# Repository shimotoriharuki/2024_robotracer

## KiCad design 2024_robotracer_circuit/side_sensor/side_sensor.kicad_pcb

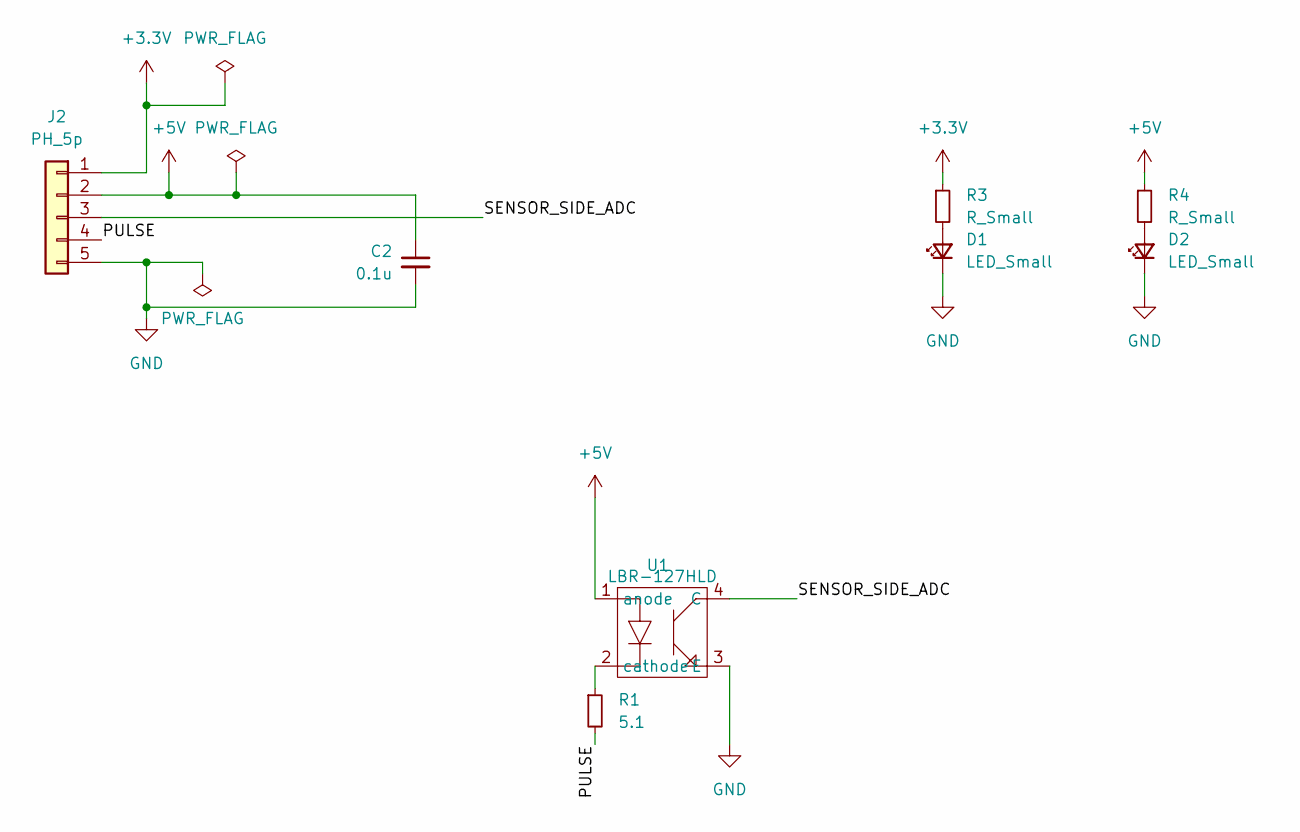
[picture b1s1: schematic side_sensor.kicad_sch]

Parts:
C2: 0.1u; C_0603_1608Metric_Pad1.08x0.95mm_HandSolder
D1, D2: LED_Small; LED_0603_1608Metric_Pad1.05x0.95mm_HandSolder
J2: PH_5p; JST_PH_B5B-PH-K_1x05_P2.00mm_Vertical
R1: 5.1; R_0603_1608Metric_Pad0.98x0.95mm_HandSolder
R3, R4: R_Small; R_0603_1608Metric_Pad0.98x0.95mm_HandSolder
U1: LBR-127HLD

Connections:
+3.3V: J2.1, R3.1
+5V: C2.1, J2.2, R4.1, U1.1 (anode)
/PULSE: J2.4, R1.2
/SENSOR_SIDE_ADC: J2.3, U1.4 (C)
GND: C2.2, D1.1 (K), D2.1 (K), J2.5, U1.3 (E)
unnamed: D1.2 (A), R3.2
unnamed: D2.2 (A), R4.2
unnamed: R1.1, U1.2 (cathode)

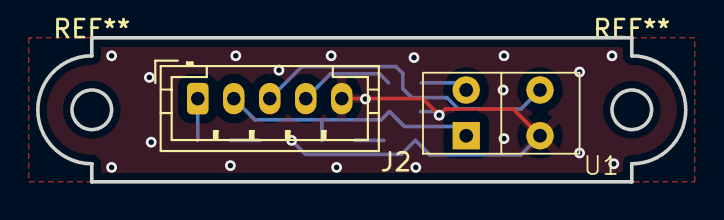
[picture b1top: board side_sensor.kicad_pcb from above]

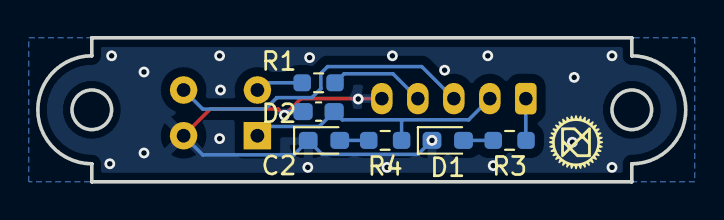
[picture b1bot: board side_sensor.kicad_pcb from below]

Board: 2 copper layers, 36.0 x 8.0 mm, 8 parts (6 on the bottom side), 8 nets.

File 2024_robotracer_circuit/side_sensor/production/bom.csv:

Designator,Footprint,Quantity,Value,LCSC Part #
C2,0603,1,0.1u,
"D1, D2",0603,2,LED_Small,
J2,JST_PH_B5B-PH-K_1x05_P2.00mm_Vertical,1,PH_5p,
R1,0603,1,4.7,
"R3, R4",0603,2,R_Small,
U1,LBR-127HLD,1,LBR-127HLD,

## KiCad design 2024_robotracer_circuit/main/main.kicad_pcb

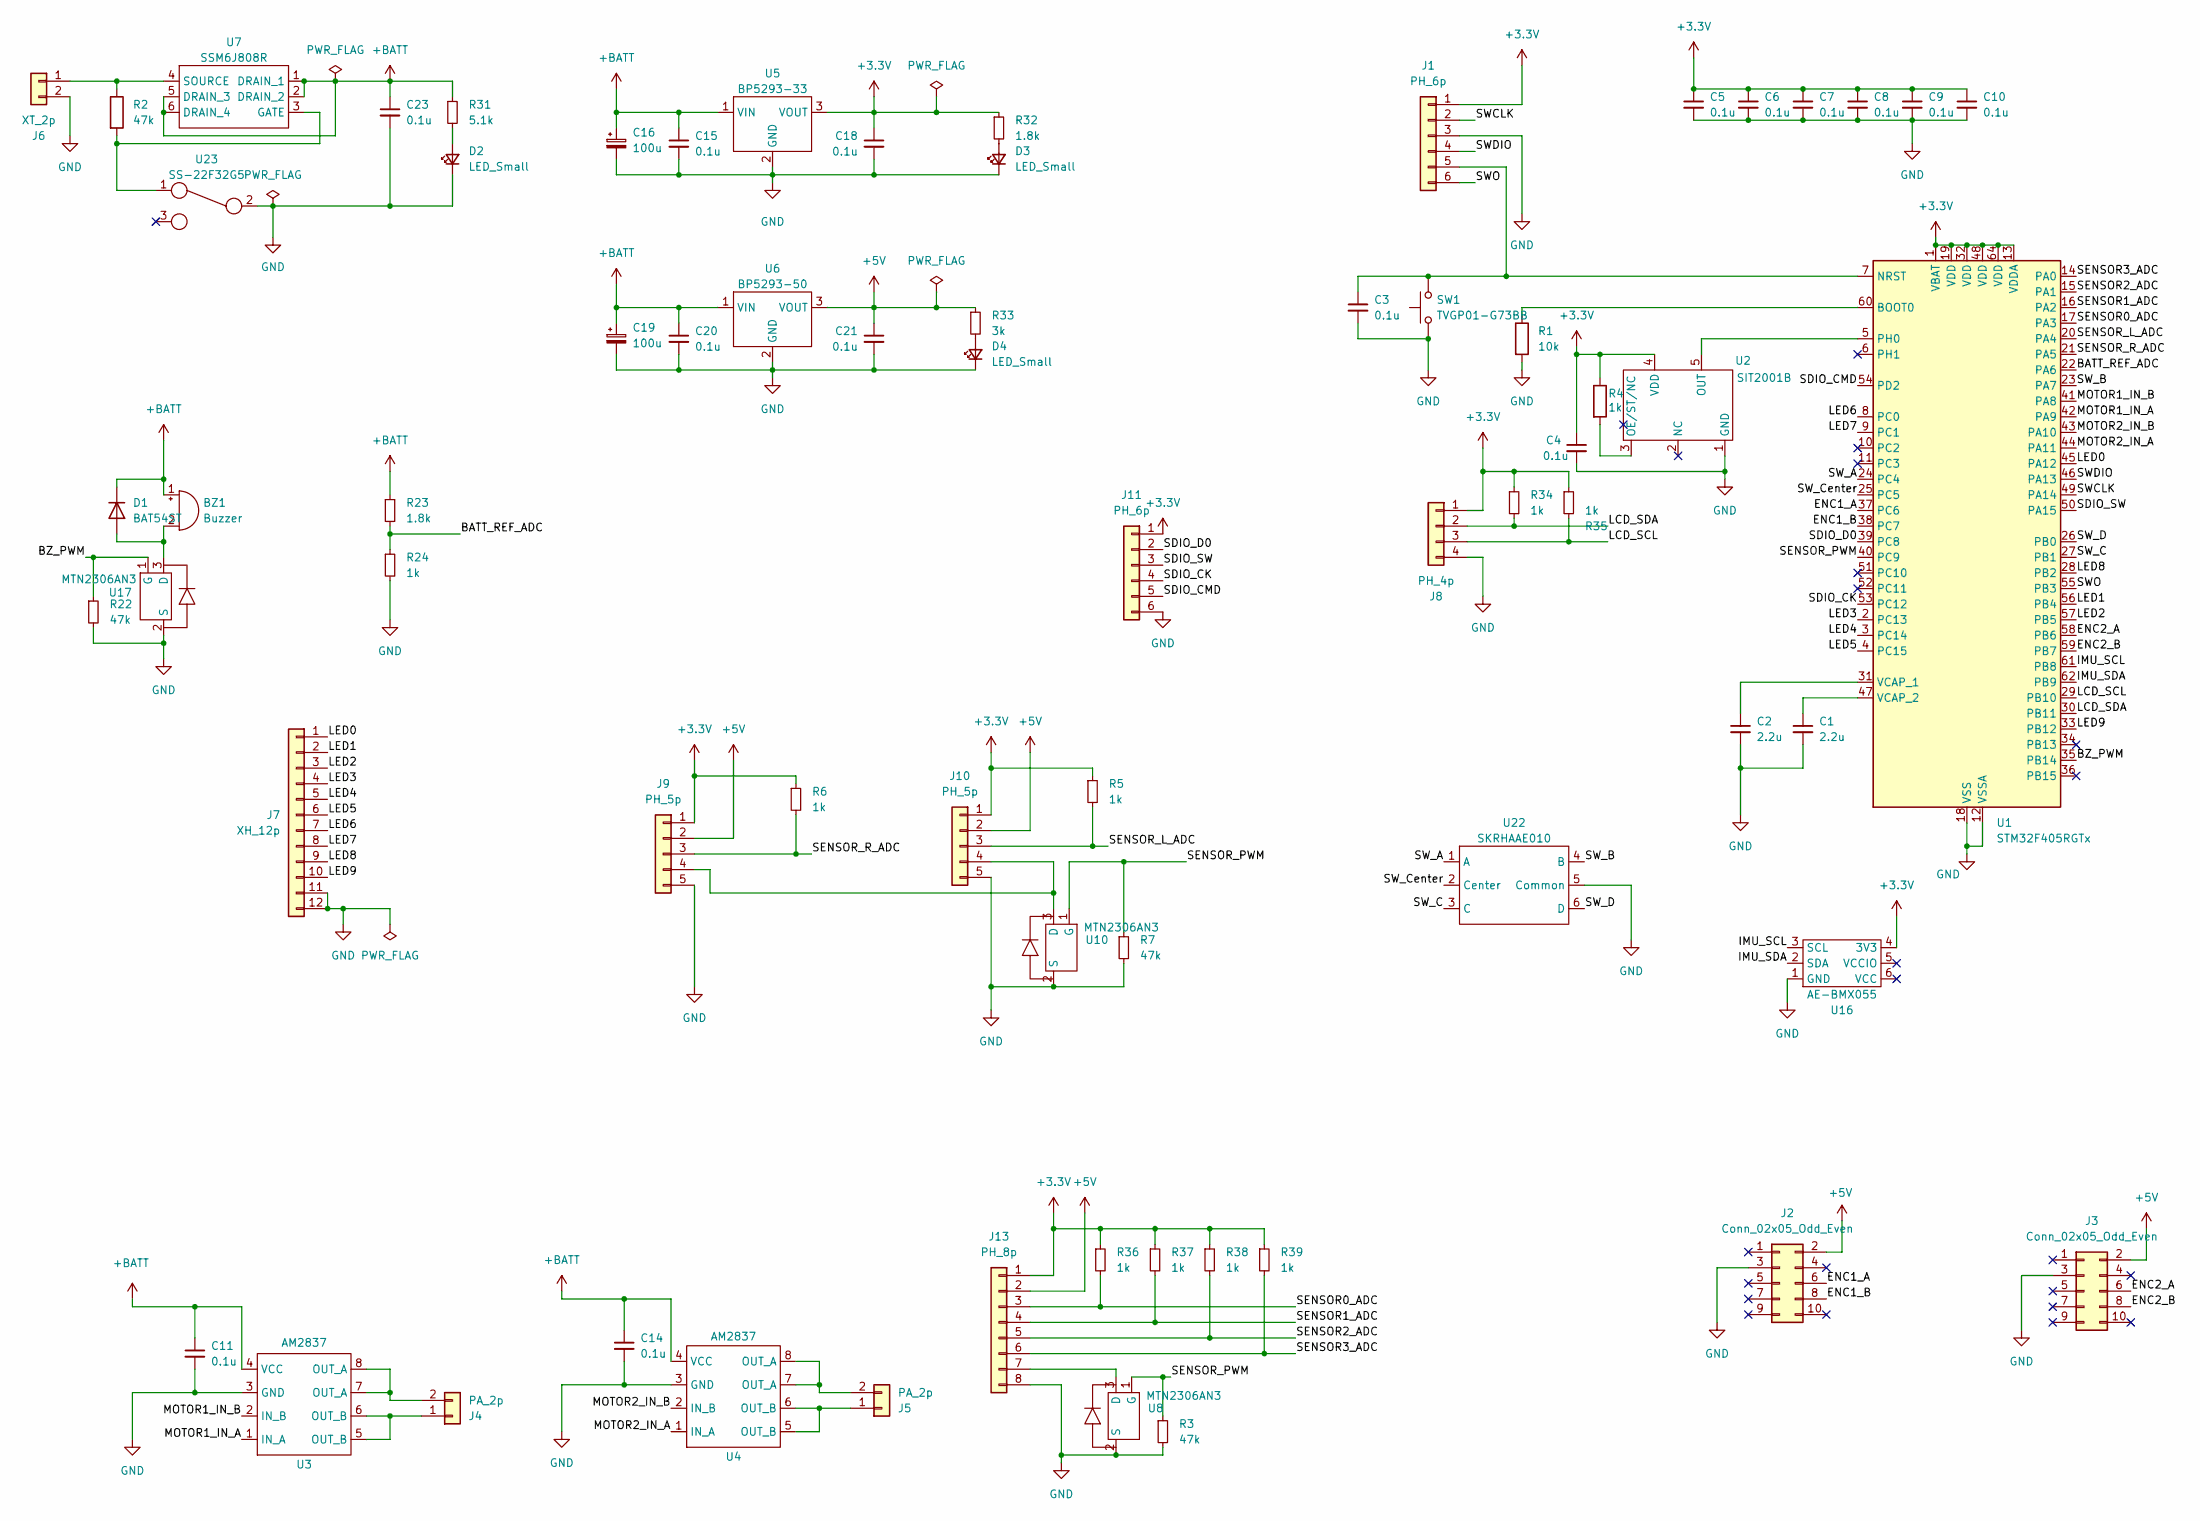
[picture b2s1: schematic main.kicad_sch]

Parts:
BZ1: Buzzer; UM1515IA085008
C1, C2: 2.2u; C_0603_1608Metric_Pad1.08x0.95mm_HandSolder
C3, C4, C5, C6, C7, C8, C9, C10, C11, C14, C15, C18, C20, C21, C23: 0.1u; C_0603_1608Metric_Pad1.08x0.95mm_HandSolder
C16, C19: 100u; CP_Elec_6.3x5.4
D1: BAT54ST; SOT-523
D2, D3, D4: LED_Small; LED_0603_1608Metric_Pad1.05x0.95mm_HandSolder
J1, J11: PH_6p; JST_PH_B6B-PH-K_1x06_P2.00mm_Vertical
J2, J3: Conn_02x05_Odd_Even; PinHeader_2x05_P1.00mm_Vertical
J4, J5: PA_2p; JST_PH_B2B-PH-K_1x02_P2.00mm_Vertical
J6: XT_2p; AMASS_XT30PW-M_1x02_P2.50mm_Horizontal
J7: XH_12p; JST_XH_B12B-XH-A_1x12_P2.50mm_Vertical
J8: PH_4p; JST_PH_B4B-PH-K_1x04_P2.00mm_Vertical
J9, J10: PH_5p; JST_PH_B5B-PH-K_1x05_P2.00mm_Vertical
J13: PH_8p; JST_PH_B8B-PH-K_1x08_P2.00mm_Vertical
R1: 10k; R_0603_1608Metric_Pad0.98x0.95mm_HandSolder
R2, R3, R7, R22: 47k; R_0603_1608Metric_Pad0.98x0.95mm_HandSolder
R4, R5, R6, R24, R34, R35, R36, R37, R38, R39: 1k; R_0603_1608Metric_Pad0.98x0.95mm_HandSolder
R23, R32: 1.8k; R_0603_1608Metric_Pad0.98x0.95mm_HandSolder
R31: 5.1k; R_0603_1608Metric_Pad0.98x0.95mm_HandSolder
R33: 3k; R_0603_1608Metric_Pad0.98x0.95mm_HandSolder
SW1: TVGP01-G73BB
U1: STM32F405RGTx; LQFP-64_10x10mm_P0.5mm
U2: SIT2001B; TSOT-23-5
U3, U4: AM2837; SOP-8_3.9x4.9mm_P1.27mm
U5: BP5293-33; BP5293-xx
U6: BP5293-50; BP5293-xx
U7: SSM6J808R; TSOP-6_1.65x3.05mm_P0.95mm
U8, U10: MTN2306AN3; TSOT-23
U16: AE-BMX055
U17: MTN2306AN3; SOT-23
U22: SKRHAAE010
U23: SS-22F32G5; PinHeader_1x03_P2.54mm_Vertical

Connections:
+3.3V: C4.1, C5.1, C6.1, C7.1, C8.1, C9.1, C10.1, C18.1, J1.1, J8.1, J9.1, J10.1, J11.1, J13.1, R4.1, R5.1, R6.1, R32.1, R34.1, R35.1, R36.1, R37.1, R38.1, R39.1, U1.1 (VBAT), U1.13 (VDDA), U1.19 (VDD), U1.32 (VDD), U1.48 (VDD), U1.64 (VDD), U2.4 (VDD), U5.3 (VOUT), U16.4 (3V3)
+5V: C21.1, J2.2, J3.2, J9.2, J10.2, J13.2, R33.1, U6.3 (VOUT)
+BATT: BZ1.1 (+), C11.1, C14.1, C15.1, C16.1, C19.1, C20.1, C23.1, D1.1 (K), R23.1, R31.1, U3.4 (VCC), U4.4 (VCC), U5.1 (VIN), U6.1 (VIN), U7.1 (DRAIN_1), U7.2 (DRAIN_2), U7.5 (DRAIN_3), U7.6 (DRAIN_4)
/BATT_REF_ADC: R23.2, R24.1, U1.22 (PA6)
/BZ_PWM: R22.1, U1.35 (PB14), U17.1 (G)
/ENC1_A: J2.6, U1.37 (PC6)
/ENC1_B: J2.8, U1.38 (PC7)
/ENC2_A: J3.6, U1.58 (PB6)
/ENC2_B: J3.8, U1.59 (PB7)
/IMU_SCL: U1.61 (PB8), U16.3 (SCL)
/IMU_SDA: U1.62 (PB9), U16.2 (SDA)
/LCD_SCL: J8.3, R35.2, U1.29 (PB10)
/LCD_SDA: J8.2, R34.2, U1.30 (PB11)
/LED0: J7.1, U1.45 (PA12)
/LED1: J7.2, U1.56 (PB4)
/LED2: J7.3, U1.57 (PB5)
/LED3: J7.4, U1.2 (PC13)
/LED4: J7.5, U1.3 (PC14)
/LED5: J7.6, U1.4 (PC15)
/LED6: J7.7, U1.8 (PC0)
/LED7: J7.8, U1.9 (PC1)
/LED8: J7.9, U1.28 (PB2)
/LED9: J7.10, U1.33 (PB12)
/MOTOR1_IN_A: U1.42 (PA9), U3.1 (IN_A)
/MOTOR1_IN_B: U1.41 (PA8), U3.2 (IN_B)
/MOTOR2_IN_A: U1.44 (PA11), U4.1 (IN_A)
/MOTOR2_IN_B: U1.43 (PA10), U4.2 (IN_B)
/SDIO_CK: J11.4, U1.53 (PC12)
/SDIO_CMD: J11.5, U1.54 (PD2)
/SDIO_D0: J11.2, U1.39 (PC8)
/SDIO_SW: J11.3, U1.50 (PA15)
/SENSOR0_ADC: J13.3, R36.2, U1.17 (PA3)
/SENSOR1_ADC: J13.4, R37.2, U1.16 (PA2)
/SENSOR2_ADC: J13.5, R38.2, U1.15 (PA1)
/SENSOR3_ADC: J13.6, R39.2, U1.14 (PA0)
/SENSOR_L_ADC: J10.3, R5.2, U1.20 (PA4)
/SENSOR_PWM: R3.1, R7.1, U1.40 (PC9), U8.1 (G), U10.1 (G)
/SENSOR_R_ADC: J9.3, R6.2, U1.21 (PA5)
/SWCLK: J1.2, U1.49 (PA14)
/SWDIO: J1.4, U1.46 (PA13)
/SWO: J1.6, U1.55 (PB3)
/SW_A: U1.24 (PC4), U22.1 (A)
/SW_B: U1.23 (PA7), U22.4 (B)
/SW_C: U1.27 (PB1), U22.3 (C)
/SW_Center: U1.25 (PC5), U22.2 (Center)
/SW_D: U1.26 (PB0), U22.6 (D)
GND: C1.2, C2.2, C3.2, C4.2, C5.2, C6.2, C7.2, C8.2, C9.2, C10.2, C11.2, C14.2, C15.2, C16.2, C18.2, C19.2, C20.2, C21.2, C23.2, D2.1 (K), D3.1 (K), D4.1 (K), J1.3, J2.3, J3.3, J6.2, J7.11, J7.12, J8.4, J9.5, J10.5, J11.6, J13.8, R1.2, R3.2, R7.2, R22.2, R24.2, SW1.1, U1.12 (VSSA), U1.18 (VSS), U1.63 (VSS), U2.1 (GND), U3.3 (GND), U4.3 (GND), U5.2 (GND), U6.2 (GND), U8.2 (S), U10.2 (S), U16.1 (GND), U17.2 (S), U22.5 (Common), U23.2
unnamed: BZ1.2 (-), D1.2 (A), U17.3 (D)
unnamed: D2.2 (A), R31.2
unnamed: D3.2 (A), R32.2
unnamed: D4.2 (A), R33.2
unnamed: C3.1, J1.5, SW1.2, U1.7 (NRST)
unnamed: J4.1, U3.5 (OUT_B), U3.6 (OUT_B)
unnamed: J4.2, U3.7 (OUT_A), U3.8 (OUT_A)
unnamed: J5.1, U4.5 (OUT_B), U4.6 (OUT_B)
unnamed: J5.2, U4.7 (OUT_A), U4.8 (OUT_A)
unnamed: J6.1, R2.1, U7.4 (SOURCE)
unnamed: J9.4, J10.4, U10.3 (D)
unnamed: J13.7, U8.3 (D)
unnamed: R1.1, U1.60 (BOOT0)
unnamed: U1.5 (PH0), U2.5 (OUT)
unnamed: C2.1, U1.31 (VCAP_1)
unnamed: C1.1, U1.47 (VCAP_2)
unnamed: R4.2, U2.3 (OE/ST/NC)
unnamed: R2.2, U7.3 (GATE), U23.1

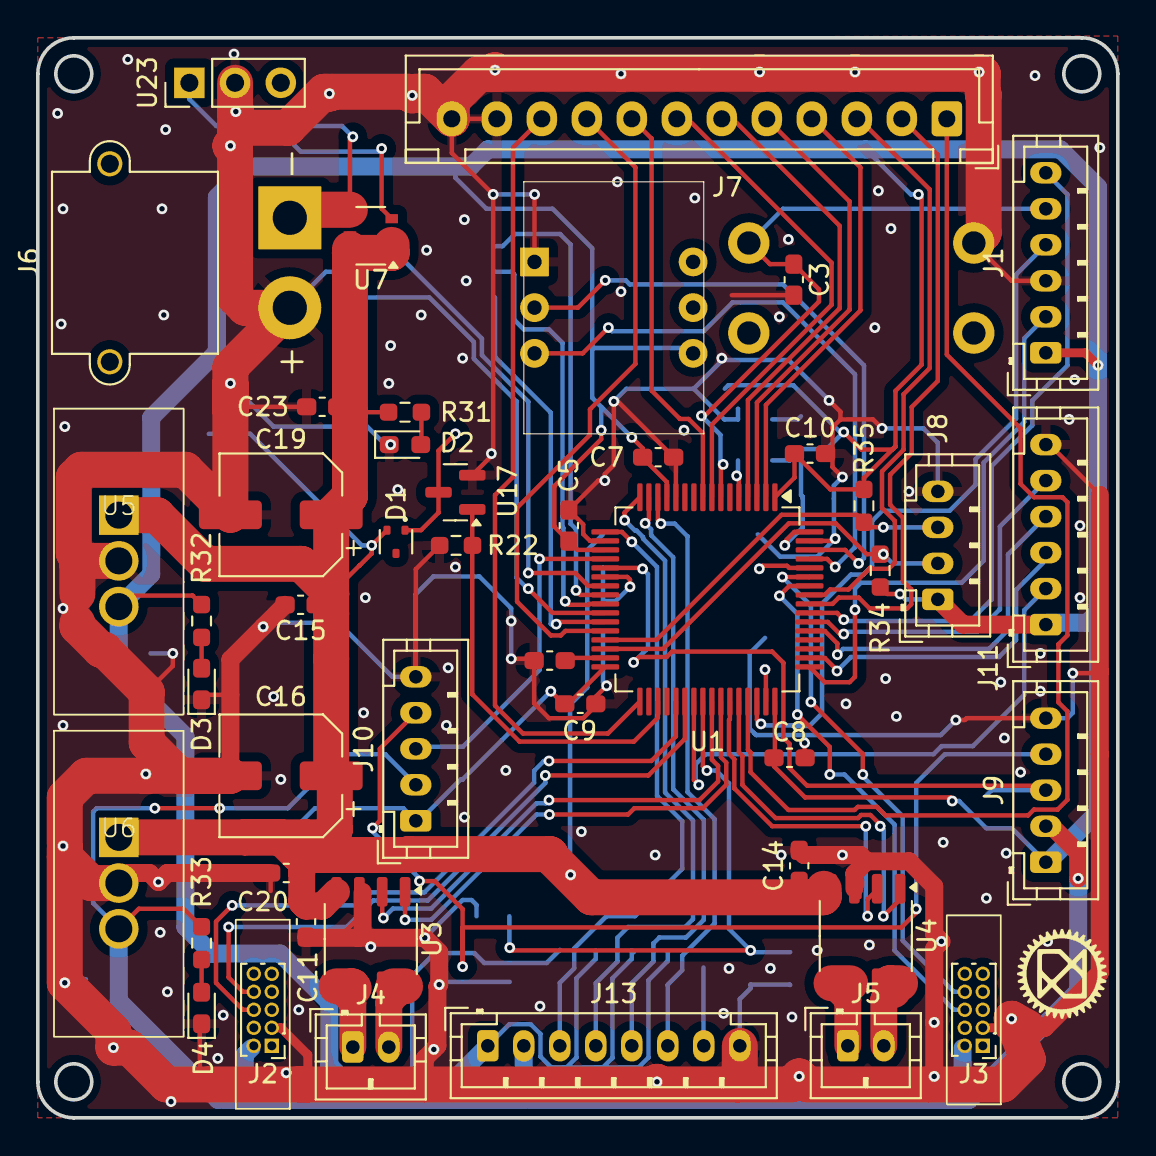
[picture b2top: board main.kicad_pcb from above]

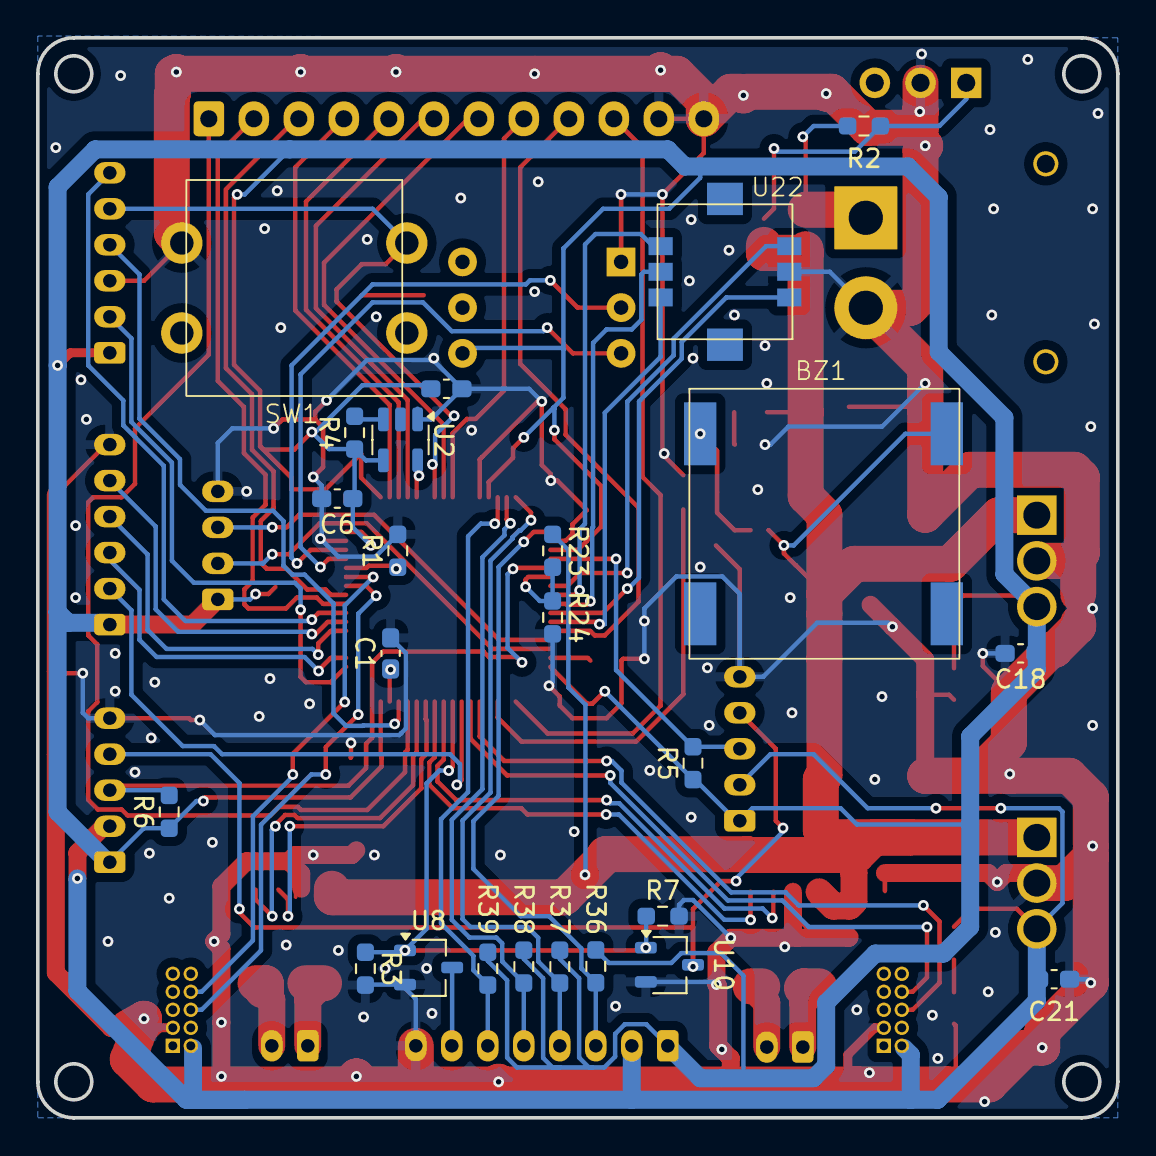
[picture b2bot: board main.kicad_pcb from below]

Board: 2 copper layers, 60.0 x 60.0 mm, 69 parts (24 on the bottom side), 65 nets.

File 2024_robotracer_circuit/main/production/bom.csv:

Designator,Footprint,Quantity,Value,LCSC Part #
BZ1,UM1515IA085008,1,Buzzer,
"C1, C2",0603,2,2.2u,
"C10, C11, C14, C15, C18, C20, C21, C23, C3, C4, C5, C6, C7, C8, C9",0603,15,0.1u,
"C16, C19",CP_Elec_6.3x5.4,2,100u,
D1,SOT-523,1,BAT54ST,
"D2, D3, D4",0603,3,LED_Small,
"J1, J11",JST_PH_B6B-PH-K_1x06_P2.00mm_Vertical,2,PH_6p,
"J10, J9",JST_PH_B5B-PH-K_1x05_P2.00mm_Vertical,2,PH_5p,
J13,JST_PH_B8B-PH-K_1x08_P2.00mm_Vertical,1,PH_8p,
"J2, J3",PinHeader_2x05_P1.00mm_Vertical,2,Conn_02x05_Odd_Even,
"J4, J5",JST_PH_B2B-PH-K_1x02_P2.00mm_Vertical,2,PA_2p,
J6,AMASS_XT30PW-M_1x02_P2.50mm_Horizontal,1,XT_2p,
J7,JST_XH_B12B-XH-A_1x12_P2.50mm_Vertical,1,HX_12p,
J8,JST_PH_B4B-PH-K_1x04_P2.00mm_Vertical,1,PH_4p,
R1,0603,1,10k,
"R2, R22, R3, R7",0603,4,47k,
R23,0603,1,1.8k,
"R24, R34, R35, R36, R37, R38, R39, R4, R5, R6",0603,10,1k,
"R31, R32, R33",0603,3,R_Small,
SW1,TVGP01-G73BB,1,TVGP01-G73BB,
U1,LQFP-64_10x10mm_P0.5mm,1,STM32F405RGTx,
"U10, U8",TSOT-23,2,MTN2306AN3,
U16,AE-BMX055,1,AE-BMX055,
U17,SOT-23,1,MTN2306AN3,
U2,TSOT-23-5,1,SIT2001B,
U22,SKRHAAE010,1, SKRHAAE010,
U23,PinHeader_1x03_P2.54mm_Vertical,1,SS-22F32G5,
"U3, U4",SOP-8_3.9x4.9mm_P1.27mm,2,AM2837,
U5,BP5293-xx,1,BP5293-33,
U6,BP5293-xx,1,BP5293-50,
U7,TSOP-6_1.65x3.05mm_P0.95mm,1,SSM6J808R,

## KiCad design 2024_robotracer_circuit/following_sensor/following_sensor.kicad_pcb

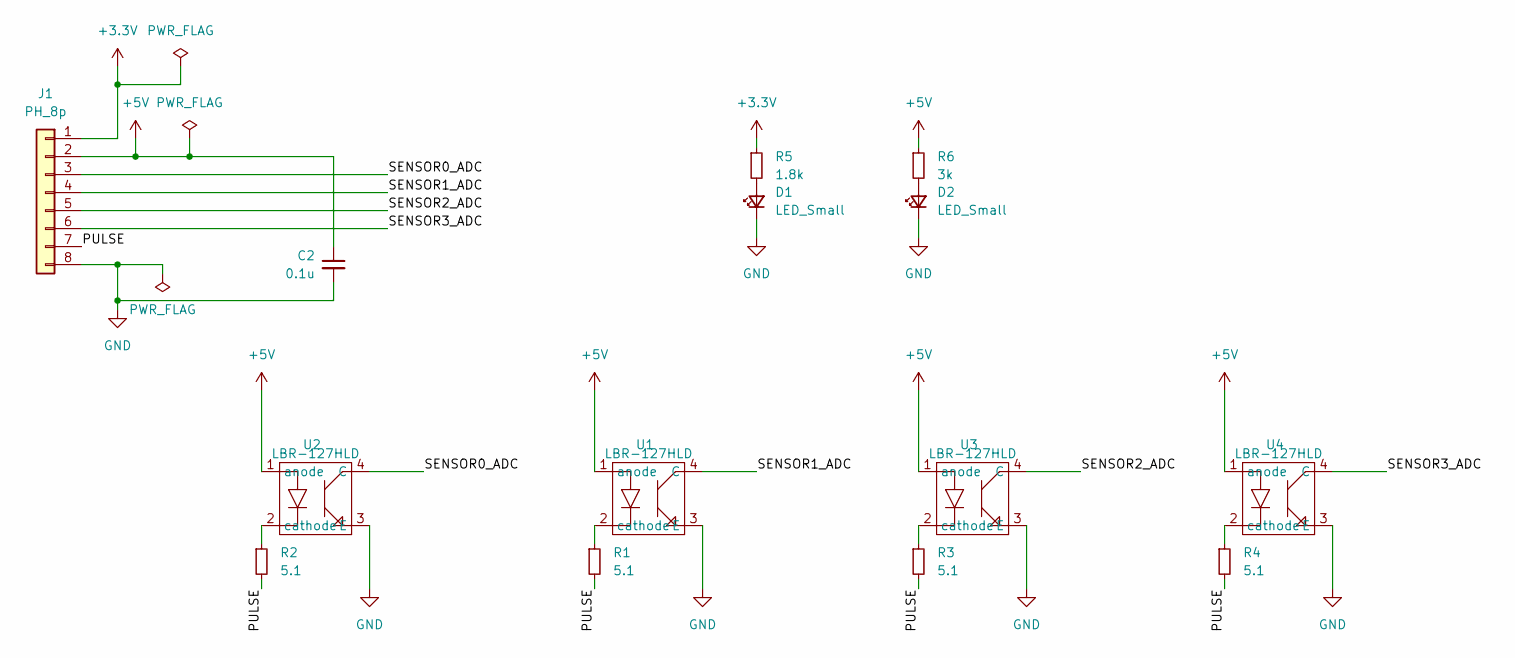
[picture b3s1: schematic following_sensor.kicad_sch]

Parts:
C2: 0.1u; C_0603_1608Metric_Pad1.08x0.95mm_HandSolder
D1, D2: LED_Small; LED_0603_1608Metric_Pad1.05x0.95mm_HandSolder
J1: PH_8p; JST_PH_B8B-PH-K_1x08_P2.00mm_Vertical
R1, R2, R3, R4: 5.1; R_0603_1608Metric_Pad0.98x0.95mm_HandSolder
R5: 1.8k; R_0603_1608Metric_Pad0.98x0.95mm_HandSolder
R6: 3k; R_0603_1608Metric_Pad0.98x0.95mm_HandSolder
U1, U2, U3, U4: LBR-127HLD

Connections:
+3.3V: J1.1, R5.1
+5V: C2.1, J1.2, R6.1, U1.1 (anode), U2.1 (anode), U3.1 (anode), U4.1 (anode)
/PULSE: J1.7, R1.2, R2.2, R3.2, R4.2
/SENSOR0_ADC: J1.3, U2.4 (C)
/SENSOR1_ADC: J1.4, U1.4 (C)
/SENSOR2_ADC: J1.5, U3.4 (C)
/SENSOR3_ADC: J1.6, U4.4 (C)
GND: C2.2, D1.1 (K), D2.1 (K), J1.8, U1.3 (E), U2.3 (E), U3.3 (E), U4.3 (E)
unnamed: D1.2 (A), R5.2
unnamed: D2.2 (A), R6.2
unnamed: R1.1, U1.2 (cathode)
unnamed: R2.1, U2.2 (cathode)
unnamed: R3.1, U3.2 (cathode)
unnamed: R4.1, U4.2 (cathode)

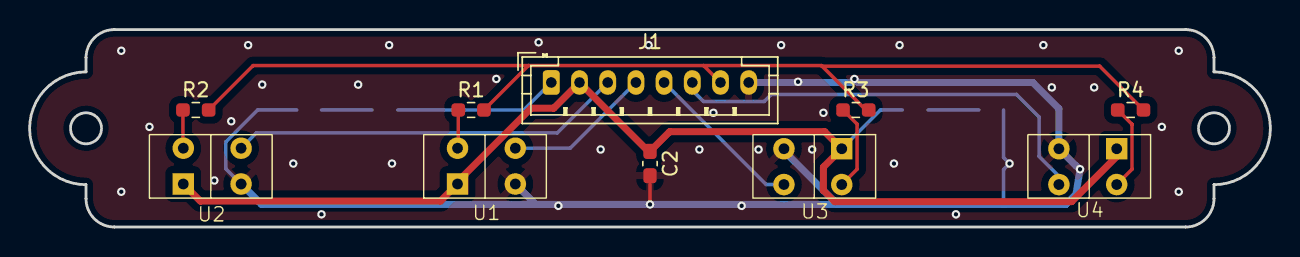
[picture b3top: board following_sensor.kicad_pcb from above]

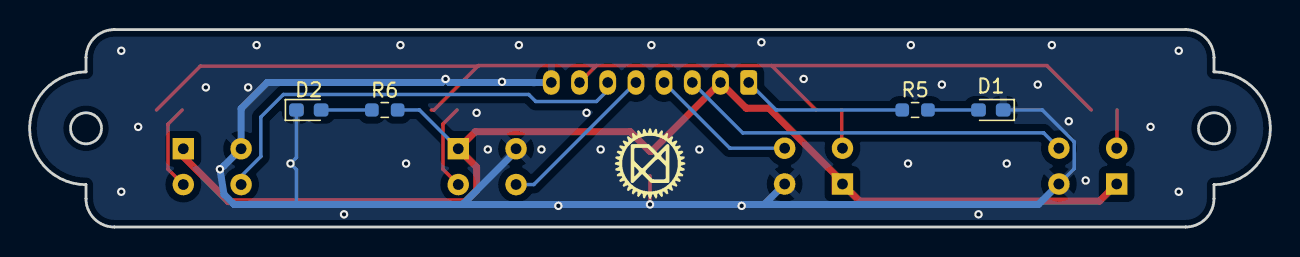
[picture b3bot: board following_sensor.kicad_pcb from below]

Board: 2 copper layers, 88.0 x 14.0 mm, 14 parts (4 on the bottom side), 14 nets.

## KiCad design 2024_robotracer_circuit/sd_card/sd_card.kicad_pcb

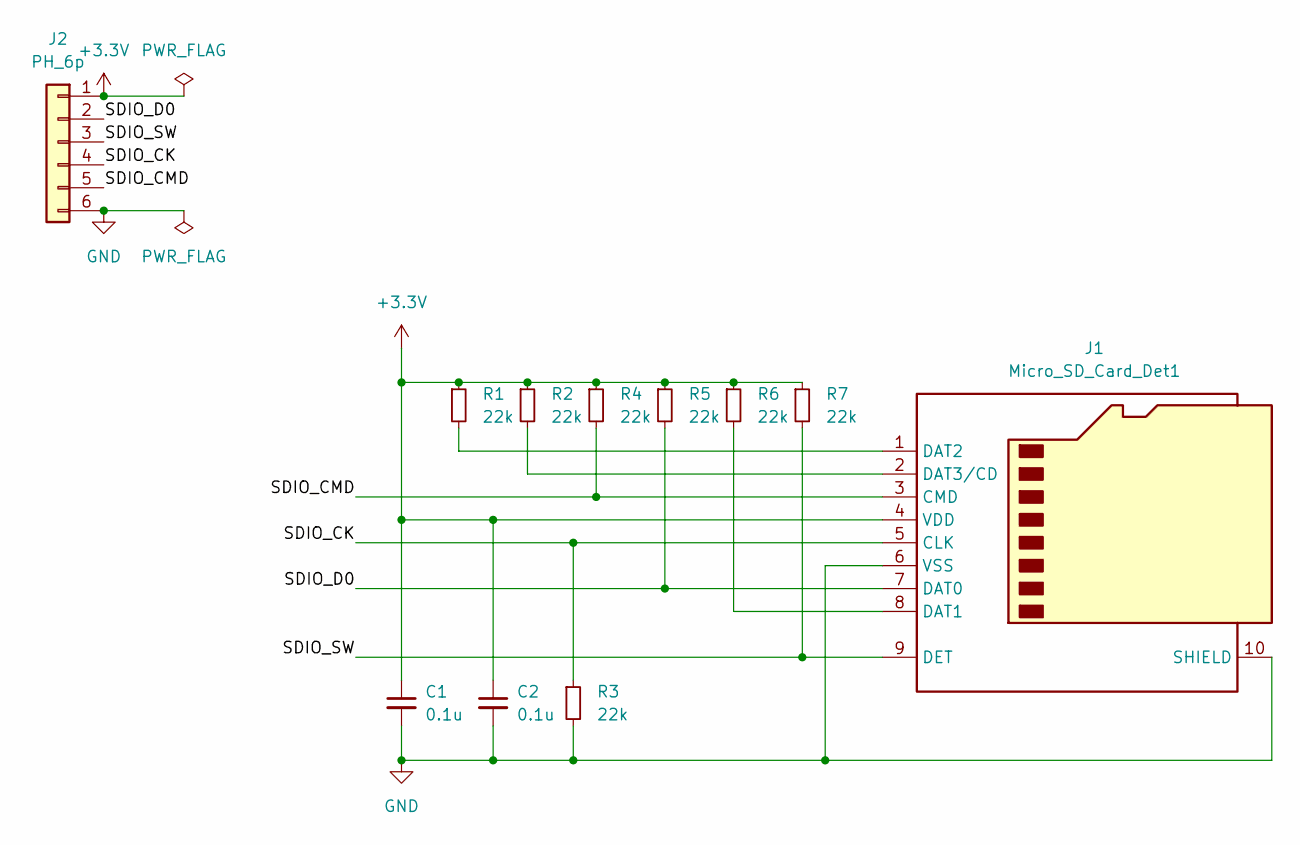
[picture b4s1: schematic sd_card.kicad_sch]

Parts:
C1, C2: 0.1u; C_0603_1608Metric_Pad1.08x0.95mm_HandSolder
J1: Micro_SD_Card_Det1; microSD_HC_Hirose_DM3AT-SF-PEJM5
J2: PH_6p; JST_PH_B6B-PH-K_1x06_P2.00mm_Vertical
R1, R2, R3, R4, R5, R6, R7: 22k; R_0603_1608Metric_Pad0.98x0.95mm_HandSolder

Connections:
+3.3V: C1.1, C2.1, J1.4 (VDD), J2.1, R1.1, R2.1, R4.1, R5.1, R6.1, R7.1
/SDIO_CK: J1.5 (CLK), J2.4, R3.1
/SDIO_CMD: J1.3 (CMD), J2.5, R4.2
/SDIO_D0: J1.7 (DAT0), J2.2, R5.2
/SDIO_SW: J1.9 (DET), J2.3, R7.2
GND: C1.2, C2.2, J1.6 (VSS), J1.10 (SHIELD), J2.6, R3.2
unnamed: J1.8 (DAT1), R6.2
unnamed: J1.1 (DAT2), R1.2
unnamed: J1.2 (DAT3/CD), R2.2

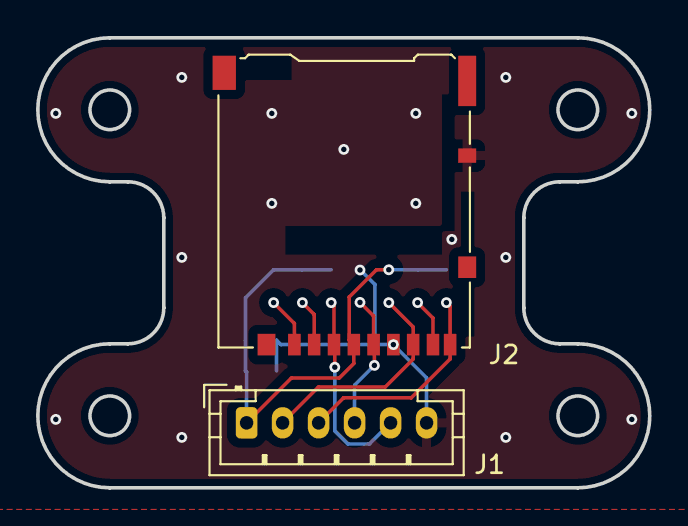
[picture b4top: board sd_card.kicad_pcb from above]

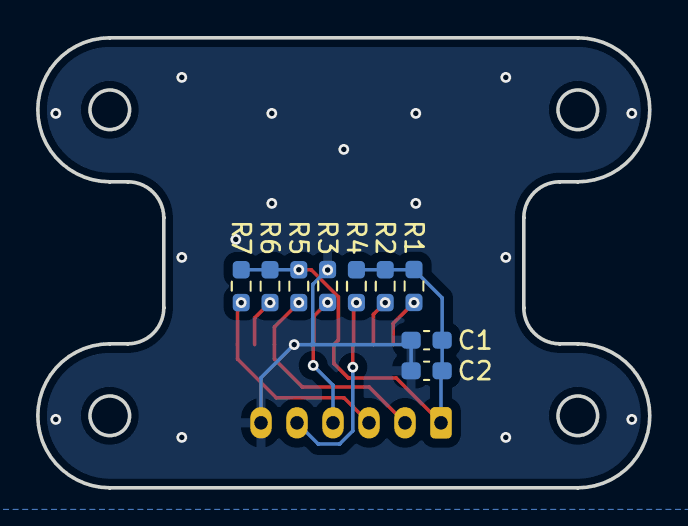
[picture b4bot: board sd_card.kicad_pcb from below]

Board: 2 copper layers, 34.0 x 25.0 mm, 11 parts (9 on the bottom side), 9 nets.

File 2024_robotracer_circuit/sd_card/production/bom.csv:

Designator,Footprint,Quantity,Value,LCSC Part #
"C1, C2",0603,2,0.1u,
J1,microSD_HC_Hirose_DM3AT-SF-PEJM5,1,Micro_SD_Card_Det1,
J2,JST_PH_B6B-PH-K_1x06_P2.00mm_Vertical,1,PH_6p,
"R1, R2, R3, R4, R5, R6, R7",0603,7,22k,

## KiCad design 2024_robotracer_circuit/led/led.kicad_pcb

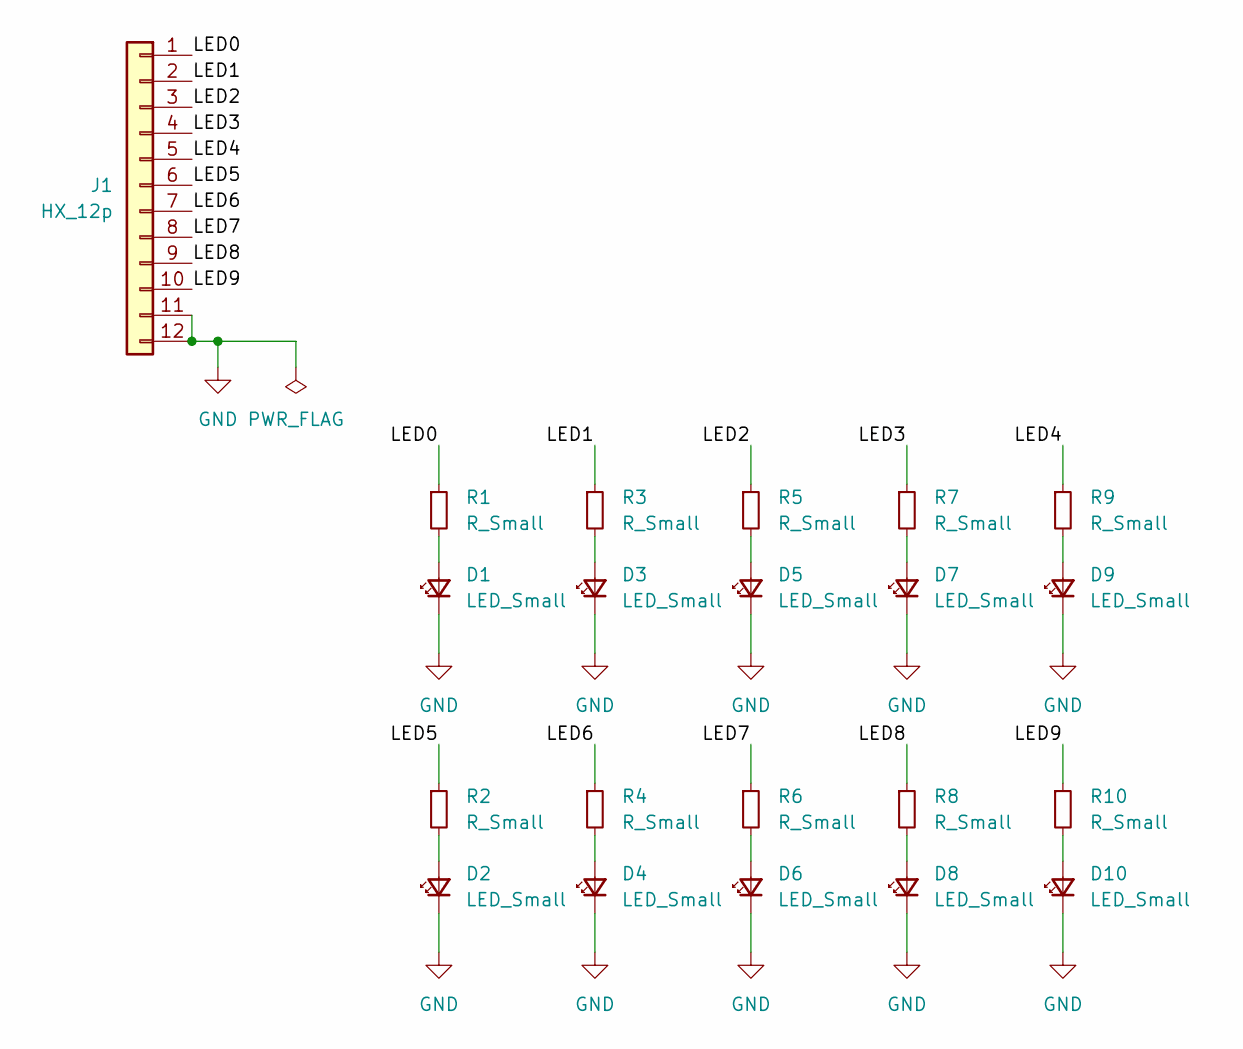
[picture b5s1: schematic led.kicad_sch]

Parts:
D1, D2, D3, D4, D5, D6, D7, D8, D9, D10: LED_Small; LED_0603_1608Metric_Pad1.05x0.95mm_HandSolder
J1: HX_12p; JST_XH_B12B-XH-A_1x12_P2.50mm_Vertical
R1, R2, R3, R4, R5, R6, R7, R8, R9, R10: R_Small; R_0603_1608Metric_Pad0.98x0.95mm_HandSolder

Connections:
/LED0: J1.1, R1.1
/LED1: J1.2, R3.1
/LED2: J1.3, R5.1
/LED3: J1.4, R7.1
/LED4: J1.5, R9.1
/LED5: J1.6, R2.1
/LED6: J1.7, R4.1
/LED7: J1.8, R6.1
/LED8: J1.9, R8.1
/LED9: J1.10, R10.1
GND: D1.1 (K), D2.1 (K), D3.1 (K), D4.1 (K), D5.1 (K), D6.1 (K), D7.1 (K), D8.1 (K), D9.1 (K), D10.1 (K), J1.11, J1.12
unnamed: D1.2 (A), R1.2
unnamed: D2.2 (A), R2.2
unnamed: D3.2 (A), R3.2
unnamed: D4.2 (A), R4.2
unnamed: D5.2 (A), R5.2
unnamed: D6.2 (A), R6.2
unnamed: D7.2 (A), R7.2
unnamed: D8.2 (A), R8.2
unnamed: D9.2 (A), R9.2
unnamed: D10.2 (A), R10.2

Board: 2 copper layers, 21 parts (0 on the bottom side), 21 nets, no tracks yet.

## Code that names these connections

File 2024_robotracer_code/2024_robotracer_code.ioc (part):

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Mcu.Name=STM32F405RGTx
Mcu.Package=LQFP64
Mcu.UserName=STM32F405RGTx
PA0-WKUP.GPIOParameters=GPIO_Label
PA0-WKUP.GPIO_Label=ADC1_IN0_SENSOR0
PA0-WKUP.Signal=ADCx_IN0
PA1.GPIOParameters=GPIO_Label
PA1.GPIO_Label=ADC1_IN1_SENSOR1
PA1.Signal=ADCx_IN1
PA10.GPIOParameters=GPIO_Label
PA10.GPIO_Label=TIM1_CH3_MOTOR2
PA10.Signal=S_TIM1_CH3
PA11.Signal=GPIO_Output
PA12.Signal=GPIO_Output
PA13.Mode=Trace_Asynchronous_SW
PA13.Signal=SYS_JTMS-SWDIO
PA14.Mode=Trace_Asynchronous_SW
PA14.Signal=SYS_JTCK-SWCLK
PA15.GPIOParameters=GPIO_Label
PA15.GPIO_Label=GPIO_INPUT_SD
PA15.Signal=GPIO_Input
PA2.GPIOParameters=GPIO_Label
PA2.GPIO_Label=ADC1_IN2_SENSOR2
PA2.Signal=ADCx_IN2
PA3.GPIOParameters=GPIO_Label
PA3.GPIO_Label=ADC1_IN3_SENSOR3
PA3.Signal=ADCx_IN3
PA4.GPIOParameters=GPIO_Label
PA4.GPIO_Label=ADC1_IN4_SENSOR_L
PA4.Signal=ADCx_IN4
PA5.GPIOParameters=GPIO_Label
PA5.GPIO_Label=ADC1_IN5_SENSOR_R
PA5.Signal=ADCx_IN5
PA6.GPIOParameters=GPIO_Label
PA6.GPIO_Label=ADC1_IN6_BATT
PA6.Signal=ADCx_IN6
PA7.GPIOParameters=GPIO_Label
PA7.GPIO_Label=GPIO_INPUT_SW0
PA7.Signal=GPIO_Input
PA8.GPIOParameters=GPIO_Label
PA8.GPIO_Label=TIM1_CH1_MOTOR1
PA8.Signal=S_TIM1_CH1
PA9.GPIOParameters=GPIO_PuPd
PA9.GPIO_PuPd=GPIO_NOPULL
PA9.Signal=GPIO_Output
PB0.GPIOParameters=GPIO_Label
PB0.GPIO_Label=GPIO_INPUT_SW3
PB0.Signal=GPIO_Input
PB1.GPIOParameters=GPIO_Label
PB1.GPIO_Label=GPIO_INPUT_SW4
PB1.Signal=GPIO_Input
PB10.GPIOParameters=GPIO_Label
PB10.GPIO_Label=I2C2_SCL_LCD
PB10.Mode=I2C
PB10.Signal=I2C2_SCL
PB11.GPIOParameters=GPIO_Label
PB11.GPIO_Label=I2C2_SDA_LCD
PB11.Mode=I2C
PB11.Signal=I2C2_SDA
PB12.Signal=GPIO_Output
PB13.GPIOParameters=GPIO_Label
PB13.GPIO_Label=SPI2_SCK_GP
PB13.Mode=Full_Duplex_Master
PB13.Signal=SPI2_SCK
PB14.GPIOParameters=GPIO_Label
PB14.GPIO_Label=TIM12_CH1_BZ
PB14.Signal=S_TIM12_CH1
PB15.GPIOParameters=GPIO_Label
PB15.GPIO_Label=TIM12_CH2_GP
PB15.Signal=S_TIM12_CH2
PB2.Signal=GPIO_Output
PB3.Mode=Trace_Asynchronous_SW
PB3.Signal=SYS_JTDO-SWO
PB4.Signal=GPIO_Output
PB5.Signal=GPIO_Output
PB6.GPIOParameters=GPIO_Label
PB6.GPIO_Label=TIM4_CH1_ENC1
PB6.Signal=S_TIM4_CH1
PB7.GPIOParameters=GPIO_Label
PB7.GPIO_Label=TIM4_CH2_ENC1
PB7.Signal=S_TIM4_CH2
PB8.GPIOParameters=GPIO_Label
PB8.GPIO_Label=I2C1_SCL_IMU
PB8.Mode=I2C
PB8.Signal=I2C1_SCL
PB9.GPIOParameters=GPIO_Label
PB9.GPIO_Label=I2C1_SDA_IMU
PB9.Mode=I2C
PB9.Signal=I2C1_SDA
PC0.Signal=GPIO_Output
PC1.Signal=GPIO_Output
PC10.Mode=Asynchronous
PC10.Signal=USART3_TX
PC11.Mode=Asynchronous
PC11.Signal=USART3_RX
PC12.Mode=SD_1_bit
PC12.Signal=SDIO_CK
PC13-ANTI_TAMP.Signal=GPIO_Output
PC14-OSC32_IN.Signal=GPIO_Output
PC15-OSC32_OUT.Signal=GPIO_Output
PC2.GPIOParameters=GPIO_Label
PC2.GPIO_Label=SPI2_MISO_GP
PC2.Mode=Full_Duplex_Master
PC2.Signal=SPI2_MISO
PC3.GPIOParameters=GPIO_Label
PC3.GPIO_Label=SPI2_MOSI_GP
PC3.Mode=Full_Duplex_Master
PC3.Signal=SPI2_MOSI
PC4.GPIOParameters=GPIO_Label
PC4.GPIO_Label=GPIO__INPUT_SW1
PC4.Signal=GPIO_Input
PC5.GPIOParameters=GPIO_Label
PC5.GPIO_Label=GPIO_INPUT_SW2
PC5.Signal=GPIO_Input
PC6.GPIOParameters=GPIO_Label
PC6.GPIO_Label=TIM3_CH1_ENC2
PC6.Signal=S_TIM3_CH1
PC7.GPIOParameters=GPIO_Label
PC7.GPIO_Label=TIM3_CH2_ENC2
PC7.Signal=S_TIM3_CH2
PC8.Mode=SD_1_bit
PC8.Signal=SDIO_D0
PC9.GPIOParameters=GPIO_Label
PC9.GPIO_Label=TIM8_CH4_SENSOR_PWM
PC9.Signal=S_TIM8_CH4
PD2.Mode=SD_1_bit
PD2.Signal=SDIO_CMD
PH0-OSC_IN.Mode=HSE-External-Oscillator
PH0-OSC_IN.Signal=RCC_OSC_IN
PH1-OSC_OUT.Mode=HSE-External-Oscillator
PH1-OSC_OUT.Signal=RCC_OSC_OUT
RCC.HSE_VALUE=20000000
RCC.SYSCLKFreq_VALUE=168000000
RCC.SYSCLKSource=RCC_SYSCLKSOURCE_PLLCLK
board=custom

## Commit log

2024-06-08 回路すすめた
2024-06-08 コード追加
2024-06-08 ディレクトリ名変更
2024-06-11 Create LICENSE
2024-06-12 ピン割り当て
2024-06-12 gitignore
2024-06-13 デザインルールOK
2024-06-13 ピン割り当て変更
2024-06-14 フットプリント割り当て中
2024-06-17 とちゅう
2024-06-21 フットプリント割り当ておわり
2024-06-21 基板わけた
2024-06-21 SDカード分けた
2024-06-21 パターン引き中
2024-06-26 LED基板分けた
2024-06-29 配線途中
2024-06-30 マイコン向き変えたい
2024-06-30 マイコン回転させる前
2024-06-30 LEDつながた
2024-06-30 未配線はなし
2024-07-01 エラーなし
2024-07-02 センサー
2024-07-03 サイドセンサ
2024-07-03 製造ファイル生成
2024-07-03 sdカード
2024-07-03 STEPエクスポート
2024-07-04 hoge
2024-07-13 割り込みできたけど周波数ちがそう
2024-07-13 割りこみOK
2024-07-14 周波数低くしたら発熱おさまった希ガス
2024-07-20 旧基板もってきた書き込めた
2024-07-20 IMUフル機能
2024-07-20 加速度角度OK
2024-07-20 各速度での角度と走り出す前の初期化完了
2024-07-20 PIDそれっぽくうごいた
2024-07-21 カルマンフィルタのコード追加
2024-07-21 警告なし
2024-07-21 推定角度NAN！！
2024-07-21 値でたけど変
2024-07-22 角度が発散する
2024-07-22 分散を計算
2024-07-22 やはり発進する
2024-07-23 MATLABだと発散しない
2024-07-23 offsetの単位がちがかった。直した
2024-07-23 ジャイロのみと加速度のみと比較してカルマンフィルタは確かによさそう
2024-07-23 PIDでもいい感じになった気がする
2024-07-23 codegenように書き換えた
2024-07-23 コード生成Ok
2024-07-23 ファイル変になったので整理
2024-07-23 状態フィードバック系のコードを移植
2024-07-24 一通り書いたけどxbの振子の角度を計測した値を用いるようにする必要あり
2024-07-25 エンコーダの値おかしい？
2024-07-25 デバッグの画面にある数値がおかしい？
2024-08-01 エンコーダ角速度とかOK
2024-08-01 発振する
2024-08-04 サーボ系をいったんやめる
2024-08-04 シンプルに
2024-08-04 生成したファイルいったん削除
2024-08-04 サーボなしを移植
2024-08-04 ピニオンがゆるゆるだった
2024-08-05 動いてそう。そのばにとどまらない
2024-08-05 サーボ移植
2024-08-05 サーボでも変わらずその場にとどまらん
2024-08-06 減速比修正
2024-08-06 減速比なおしたゲインにした
2024-08-07 エンコーダの符号向きが逆だった説
2024-08-07 ふらｒふらするけど倒立する
2024-08-07 これくらいがいまは限界かも
2024-08-08 デバッグ用無限ループ削除
2024-08-08 前にはすすめそう
2024-08-10 いちおうフェイルセーフつけた
2024-08-10 フェイルセーフOK
2024-08-10 いったんライントレース処理かいた
2024-08-10 トレースと倒立連動してそう
2024-08-10 前進まない
2024-08-10 前進んでる
2024-08-10 target_thetaを0から2piにしてみた
2024-08-10 ゲイン変えてみた
2024-08-10 いったんゆっくりはしる
2024-08-10 まあはしる
2024-09-07 回路を大幅修正
2024-09-29 原状復帰
2024-10-16 checkout前
2024-10-16 なんとなく速度ゲインあわせた
2024-10-18 ライントレースできそう
2024-10-18 倒立ライントレースできてそう
2024-10-21 ゴールできそう
2024-10-21 倒立しない
2024-10-24 物理パラメータ合わせたゲイン
2024-10-27 とりあえず走りそう
2024-10-27 速くして走った
2024-10-27 記録容量ふやした
2024-10-27 二次走行うごいてそう
2024-10-27 オートスタート実装中
2024-10-27 完走後にボタン押さなくていいようにした
2024-10-27 オートスタートできた
2024-10-27 緊急停止した時はボタンおさなきゃ次へ進まないようにした
2024-10-27 倒立テストで倒れるまで続くようにしたつもり
2024-10-30 状態変数ログとって可視化した。theta_wとdtheta_wおかしい？
2024-10-30 起電力定数が違った説
2024-10-30 いい感じのゲインにたまたまなった？
2024-11-01 倒立してると進まん
2024-11-02 減速下げた
2024-11-04 ログファイル追加
2024-11-07 サーボ系いったんなくした
2024-12-02 位置フィードバックなくしたい
2024-12-02 ゲイン手合わせ中
2024-12-04 thetawのゲイン超低くした
2024-12-04 PDゲイン調整してだめそうなら角速度のエラーを状態変数に加える
2024-12-05 PIDじゃむりそう
2024-12-05 ゲイン調整中
2024-12-14 dtheta_wがおかしい？
2024-12-14 状態編巣の単位違う？
2024-12-14 わからん
2024-12-28 inputを変換してるところがちがう？
2024-12-28 とまった
2024-12-28 とまらんくなったいみわからん
2024-12-31 休ませたらよさげ？
2025-01-05 倒れた判定常にするようにした
2025-01-05 すぐ止まるようにした
2025-01-05 初期角度をオフセットした
2025-01-05 重心高さ変更
2025-01-05 物理パラメータ確認してみる？おもり追加したから
2025-01-11 物理パラメータ見直した
2025-01-13 タイヤ戻しtあ
2025-01-14 タイヤ変更
2025-01-14 merge前
2025-01-19 ADCとTimerの連携はむずそうなのでセンサ抵抗あげて連続で読めるようにする
2025-01-19 そのまえにConfigOC.Pulseを設定するやつやってみる
2025-01-20 PWMでてる
2025-01-20 PWMでてADCもできてるけどタイミングがわからん
2025-01-20 あまあまあ読める
2025-01-20 ゆっくりだと[200~HAL_TIM_PWM_PulseFinishedCallback~のほうがよさあそう
2025-01-20 点滅させなくても読めそう
2025-01-23 物理パラメータ変更
2025-01-23 なんとなく前進むこともある
2025-01-24 倒立はよい
2025-01-24 前後するする
2025-01-24 一定速度で走った！！
2025-01-24 速度速くしてもOKそう
2025-01-24 その場で止まるようにもなった！
2025-01-25 止まることはいったんあきらめる
2025-01-25 センサー読めた
2025-01-25 なぜか発振
2025-01-25 ゲインが変になってた
2025-01-25 ラインセンサの緊急停止とゴール判定をあとは確認
2025-01-25 緊急停止まだ
2025-01-26 走ったし緊急停止もOK
2025-01-26 とりあえずオートスタート作った
2025-01-26 オートスタートのとき異常終了したらつづきやらないようにしたつもり
2025-01-26 クロスライン時ライントレース切ったつもり
2025-01-27 ゲイン変えれるようした。その場でとまらない
2025-01-27 なんとなく止まるゲイン
2025-01-27 ちょっとうるさいけどちゃんと止まるのでよしとする
2025-01-29 たぶんゴール後にその場で止まる処理入った
2025-02-16 ゴール後に止まりそうではあるがゲインが微妙
2025-02-16 8Vくらいできれいにとまる神ゲインかも
2025-02-16 今のところ調子いいゲイン
2025-02-16 これもよさげなゲイン
2025-02-16 SIDE_LINE_IGNORE_DISTANCE変更
2025-02-16 ゲイン変わってないけどうるさくなったり後ろ行っちゃったり
2025-02-16 クロスライン無視処理復活させてみた。無理そうなら消す
2025-02-16 isCrossLineをちゃんとした
2025-02-16 クロスライン無視の距離短くした
2025-02-16 クロス無視はいい感じになってそう
2025-02-16 電圧さっきより高いのでdutyの比率を変えてみる
2025-02-16 比率変えたら同じような動きになるかな
2025-02-16 ちょいゲイン変えた
2025-02-16 ましになった希ガス
2025-02-16 ゲインちょい低く
2025-02-16 一回だけで止まるモードの停止処理追加したつもり
2025-02-16 最後はちゃんと制御切るようになった
2025-02-16 止まるときうるさいけどまあ止まるし走る
2025-02-22 止まる距離長くした
2025-02-22 止まるだけモード作ったつもり
2025-02-23 止まる時間短くとゲイン下げた
2025-02-23 いい感じなのでこれでいく
2025-08-22 simscape追加
2025-08-30 スクリプト追加
